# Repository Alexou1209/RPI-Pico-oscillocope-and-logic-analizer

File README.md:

# Portable Pocket Oscilloscope & Logic Analyzer

A compact, hardware-isolated digital oscilloscope and logic analyzer built around the Raspberry Pi Pico 2 (RP2350) microcontroller. This project focuses on high-speed ADC sampling, hardware-level circuit protection, and signal conditioning frontend design.

## Project Status: Active Development (Phase 2)

* **Phase 1: Hardware Design (Completed):** first version of the PCB schematic and routing finalized in KiCad. 3D enclosure designed in FreeCAD.
* **Phase 2: Prototyping & Assembly (In Progress):** Component sourcing (BOM) completed. Currently awaiting parts for manual SMT assembly and initial hardware bring-up/validation.
* **Phase 3: Firmware Integration (Upcoming):** Flashing and calibrating the modified sigrok-pico core firmware.

## System Architecture Overview

The system captures analog and digital signals, conditions them through an analog frontend to match the safe input voltage range of the RP2350, and streams the processed data over USB to a host PC using PulseView.

---

## Hardware Engineering

### 1. Circuit Design & PCB Routing (`/hardware`)
Designed and routed a custom single-board layout using **KiCad**, prioritizing signal isolation and noise reduction.
* **Analog Frontend (AFE):** Implemented an input impedance matching network (1 MΩ standard) paired with an operational amplifier configuration for signal attenuation and shifting, allowing safe sampling of signals beyond the microcontroller's native 3.3V limit.
* **Overvoltage & Transient Protection:** Integrated clamping diodes to protect the RP2350 GPIO and ADC pins from accidental overvoltage spikes.
* **USB Port Isolation:** Implemented galvanic isolation on the USB data and power lines to decouple the circuit from the host PC's ground loop, mitigating switching noise and protecting test equipment.

---

## Firmware & Software Architecture (`/firmware`)

The main software is based on the work of [sigrok-pico](https://github.com/pico-coder/sigrok-pico) with only minor changes in the firmware to output the read value after voltage attenuation. 

---

## Repository Directory Structure

```text
├── 3d_models/                # FreeCAD project files for the case, and step model of the PCB
├── docs/                     # Schematics (PDF/PNG), layout captures, and component datasheets
├── hardware/                 # KiCad project files (Schematics, PCB layout, footprints)
└── firmware/                 # Microcontroller source code (C/C++) and build files
```

---

## Contributors & Credits
* **Alexandre Dionne** – Solo Hardware conception, analog frontend topology design, and firmware modification.
* [**sigrok-pico project team**](https://github.com/pico-coder/sigrok-pico) for the main firmware.

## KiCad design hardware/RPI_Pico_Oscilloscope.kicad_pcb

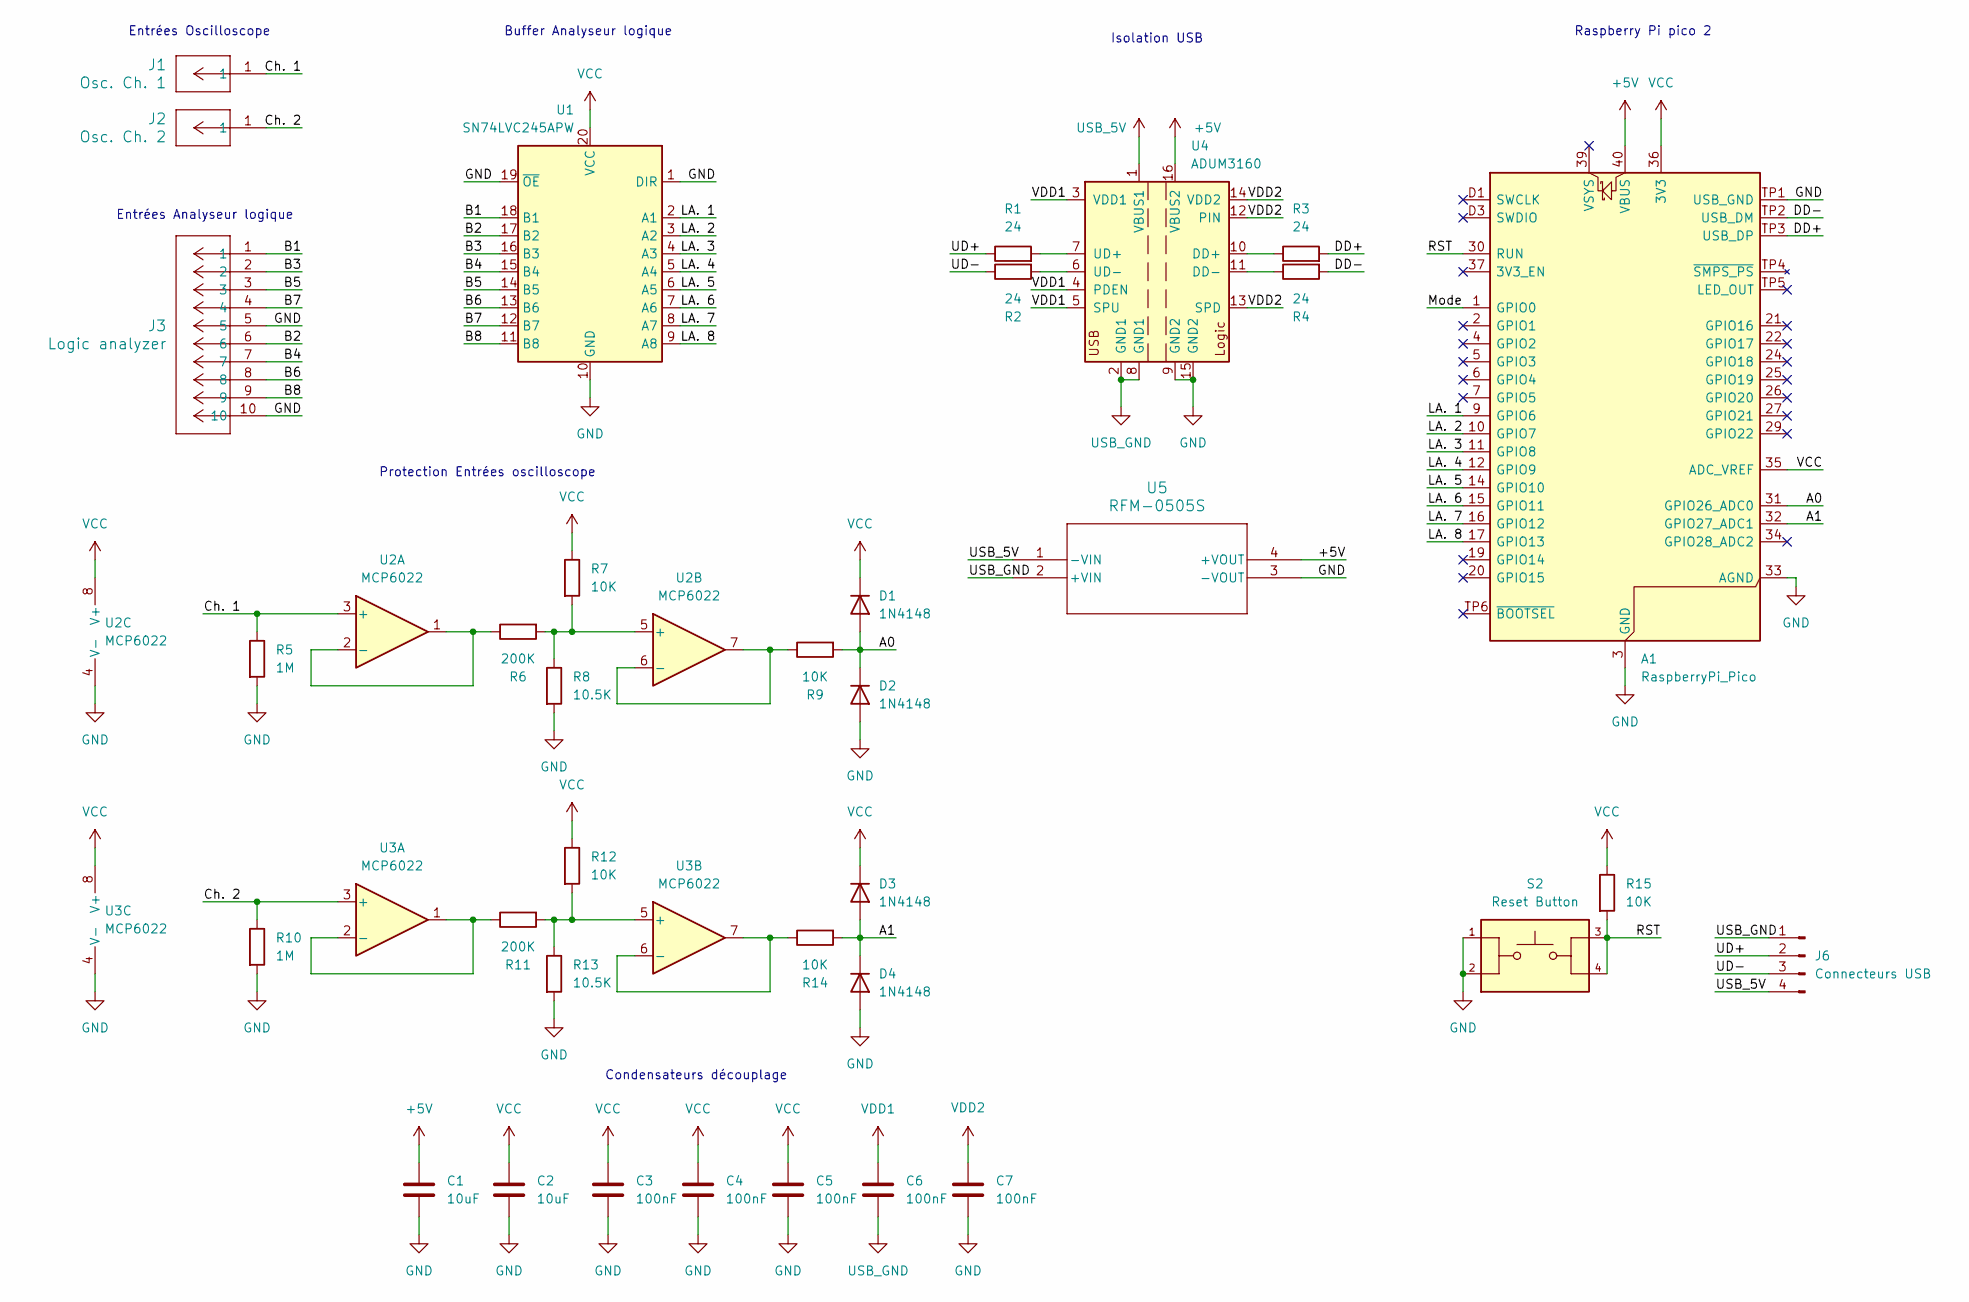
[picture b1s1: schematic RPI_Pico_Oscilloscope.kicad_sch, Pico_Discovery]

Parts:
A1: RaspberryPi_Pico; RaspberryPi_Pico_SMD
C1, C2: 10uF; C_0603_1608Metric_Pad1.08x0.95mm_HandSolder
C3, C4, C5, C6, C7: 100nF; C_0603_1608Metric_Pad1.08x0.95mm_HandSolder
D1, D2, D3, D4: 1N4148; D_SOD-123
J1: Osc. Ch. 1; PinHeader_1x02_P2.54mm_Vertical
J2: Osc. Ch. 2; PinHeader_1x02_P2.54mm_Vertical
J3: Logic analyzer; CONN_302-R101_OST
J6: Connecteurs USB; PinHeader_1x04_P2.54mm_Vertical
R1, R2, R3, R4: 24; R_0603_1608Metric_Pad0.98x0.95mm_HandSolder
R5, R10: 1M; R_0603_1608Metric_Pad0.98x0.95mm_HandSolder
R6, R11: 200K; R_0603_1608Metric_Pad0.98x0.95mm_HandSolder
R7, R9, R12, R14, R15: 10K; R_0603_1608Metric_Pad0.98x0.95mm_HandSolder
R8, R13: 10.5K; R_0603_1608Metric_Pad0.98x0.95mm_HandSolder
S2: Reset Button; SW_SWT0220-016016GSA_REVA; PARTREV A
U1: SN74LVC245APW; TSSOP-20_4.4x6.5mm_P0.65mm
U2, U3: MCP6022; SOIC-8_3.9x4.9mm_P1.27mm
U4: ADUM3160; SOIC-16W_7.5x10.3mm_P1.27mm
U5: RFM-0505S; SIP4_RFM_RCP

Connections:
+5V: A1.40 (VBUS), C1.2, U4.16 (VBUS2), U5.4 (+VOUT)
/<NO NET>: A1.30 (RUN), R15.2, S2.3, S2.4
/A0: A1.31 (GPIO26_ADC0), D1.2 (A), D2.1 (K), R9.2
/A1: A1.32 (GPIO27_ADC1), D3.2 (A), D4.1 (K), R14.2
/B1: J3.1, U1.18 (B1)
/B2: J3.6, U1.17 (B2)
/B3: J3.2, U1.16 (B3)
/B4: J3.7, U1.15 (B4)
/B5: J3.3, U1.14 (B5)
/B6: J3.8, U1.13 (B6)
/B7: J3.4, U1.12 (B7)
/B8: J3.9, U1.11 (B8)
/Ch. 1: J1.1 (1_1), R5.1, U2.3 (+)
/Ch. 2: J2.1 (1_1), R10.1, U3.3 (+)
/DD+: A1.TP3 (USB_DP), R3.2
/DD-: A1.TP2 (USB_DM), R4.2
/LA. 1: A1.9 (GPIO6), U1.2 (A1)
/LA. 2: A1.10 (GPIO7), U1.3 (A2)
/LA. 3: A1.11 (GPIO8), U1.4 (A3)
/LA. 4: A1.12 (GPIO9), U1.5 (A4)
/LA. 5: A1.14 (GPIO10), U1.6 (A5)
/LA. 6: A1.15 (GPIO11), U1.7 (A6)
/LA. 7: A1.16 (GPIO12), U1.8 (A7)
/LA. 8: A1.17 (GPIO13), U1.9 (A8)
/Mode: A1.1 (GPIO0)
/UD+: J6.2, R1.1
/UD-: J6.3, R2.1
GND: A1.3 (GND), A1.8 (GND), A1.13 (GND), A1.18 (GND), A1.23 (GND), A1.28 (GND), A1.33 (AGND), A1.38 (GND), A1.D2 (GND), A1.TP1 (USB_GND), C1.1, C2.1, C3.1, C4.1, C5.1, C7.1, D2.2 (A), D4.2 (A), J3.5, J3.10, R5.2, R8.2, R10.2, R13.2, S2.1, S2.2, U1.1 (DIR), U1.10 (GND), U1.19 (~OE), U2.4 (V-), U3.4 (V-), U4.9 (GND2), U4.15 (GND2), U5.3 (-VOUT)
unnamed: R6.1, U2.1, U2.2 (-)
unnamed: R6.2, R7.2, R8.1, U2.5 (+)
unnamed: R9.1, U2.6 (-), U2.7
unnamed: R11.1, U3.1, U3.2 (-)
unnamed: R11.2, R12.2, R13.1, U3.5 (+)
unnamed: R14.1, U3.6 (-), U3.7
unnamed: R3.1, U4.10 (DD+)
unnamed: R4.1, U4.11 (DD-)
unnamed: R1.2, U4.7 (UD+)
unnamed: R2.2, U4.6 (UD-)
USB_5V: J6.4, U4.1 (VBUS1), U5.1 (-VIN)
USB_GND: C6.1, J6.1, U4.2 (GND1), U4.8 (GND1), U5.2 (+VIN)
VCC: A1.35 (ADC_VREF), A1.36 (3V3), C2.2, C3.2, C4.2, C5.2, D1.1 (K), D3.1 (K), R7.1, R12.1, R15.1, U1.20 (VCC), U2.8 (V+), U3.8 (V+)
VDD1: C6.2, U4.3 (VDD1), U4.4 (PDEN), U4.5 (SPU)
VDD2: C7.2, U4.12 (PIN), U4.13 (SPD), U4.14 (VDD2)

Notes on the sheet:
Condensateurs découplage
Raspberry Pi pico 2
Protection Entrées oscilloscope
Entrées Oscilloscope
Isolation USB
Entrées Analyseur logique
Buffer Analyseur logique

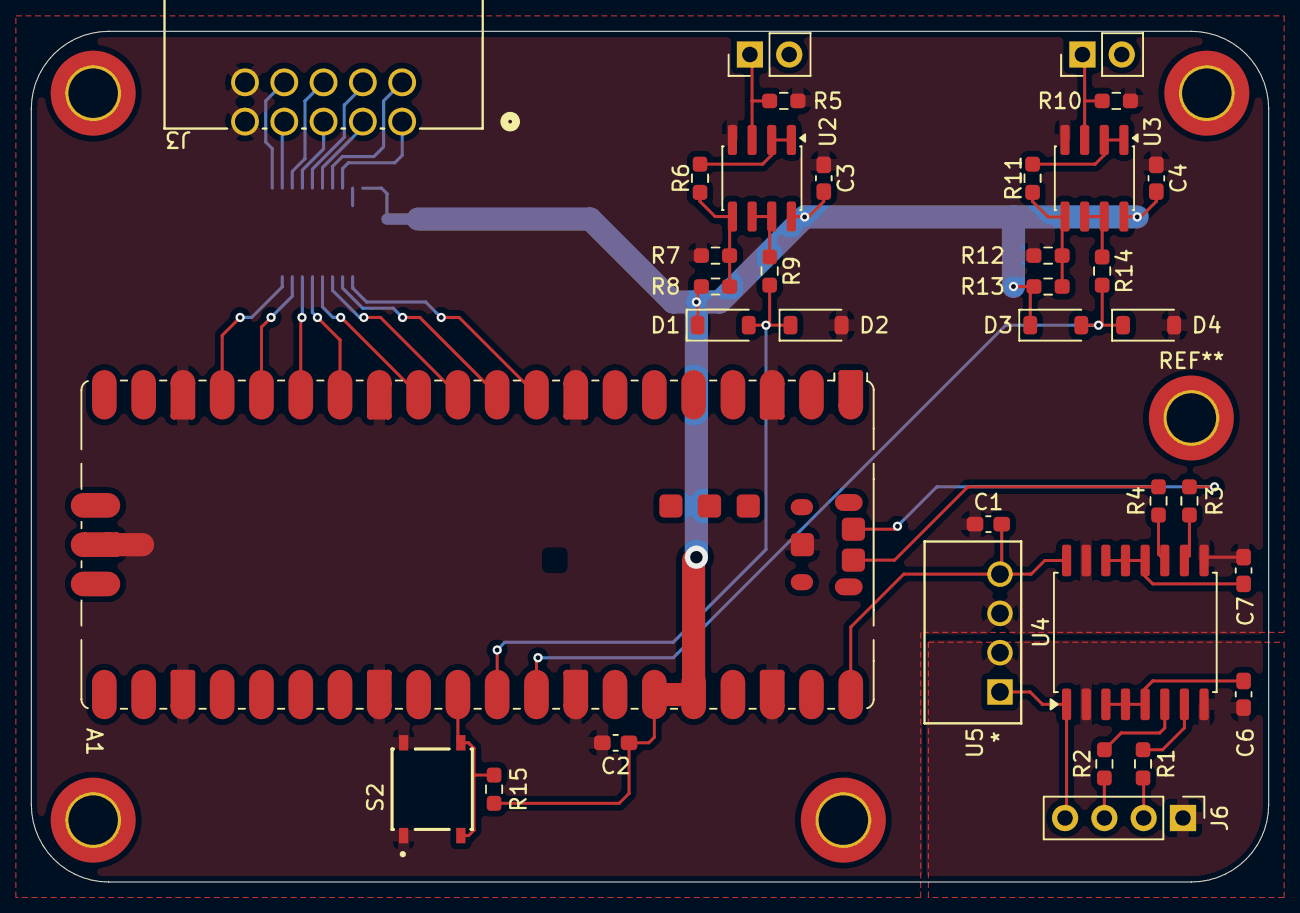
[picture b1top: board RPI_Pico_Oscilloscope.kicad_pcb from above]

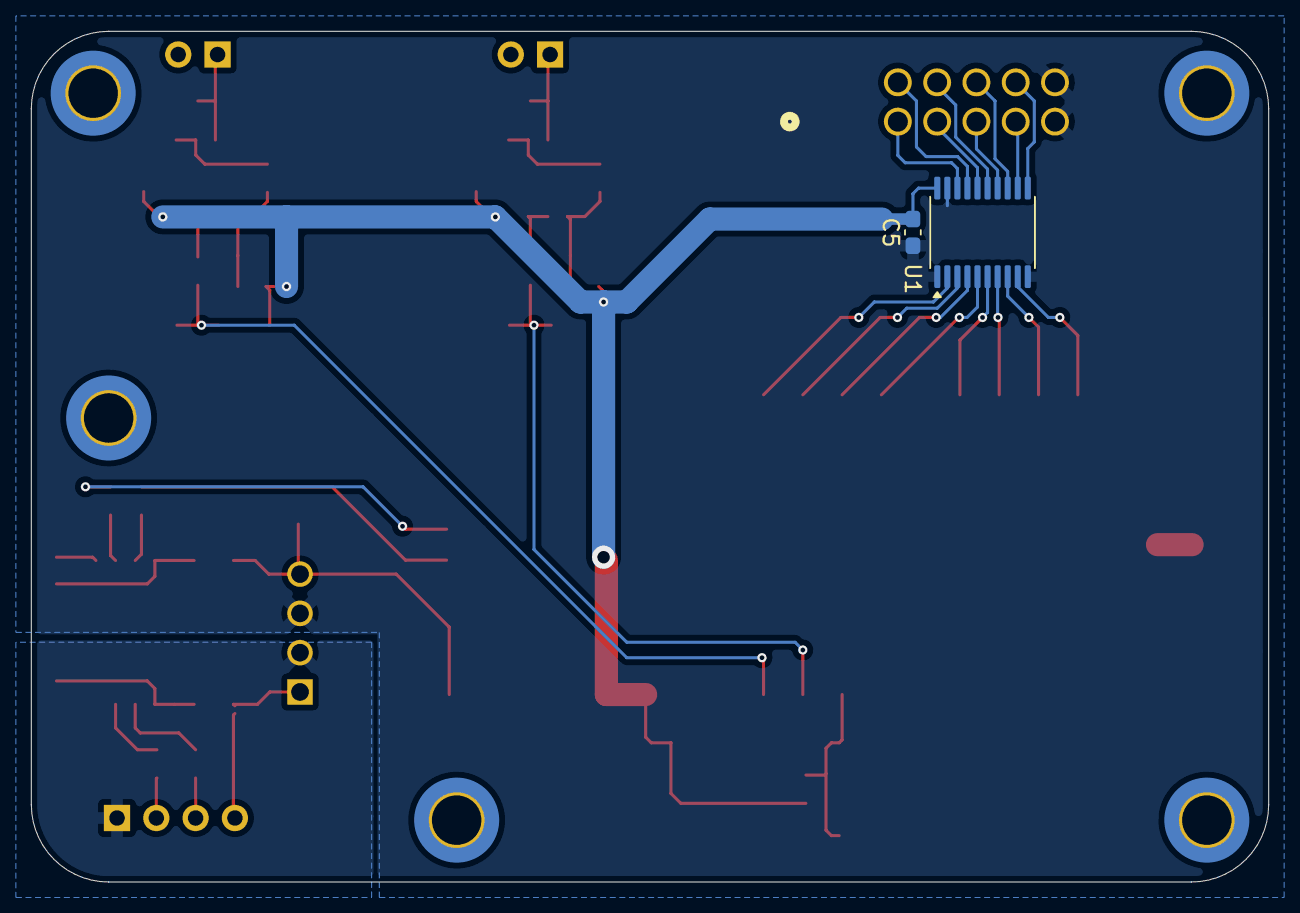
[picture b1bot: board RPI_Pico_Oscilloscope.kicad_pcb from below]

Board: 2 copper layers, 80.0 x 55.0 mm, 37 parts (2 on the bottom side), 42 nets.
